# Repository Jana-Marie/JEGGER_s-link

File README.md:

# JEGGER s-link

[https://twitter.com/_Jana_Marie/status/1245725762642206728](https://twitter.com/_Jana_Marie/status/1245725762642206728)

-------

[https://github.com/ARMmbed/DAPLink](https://github.com/ARMmbed/DAPLink)

-------

https://github.com/blacksphere/blackmagic/wiki

-------

[.](https://weekly-geekly.github.io/articles/442290/index.html)
[.](https://www.segger.com/products/debug-probes/j-link/models/other-j-links/st-link-on-board/)

Go figure it out for yourself

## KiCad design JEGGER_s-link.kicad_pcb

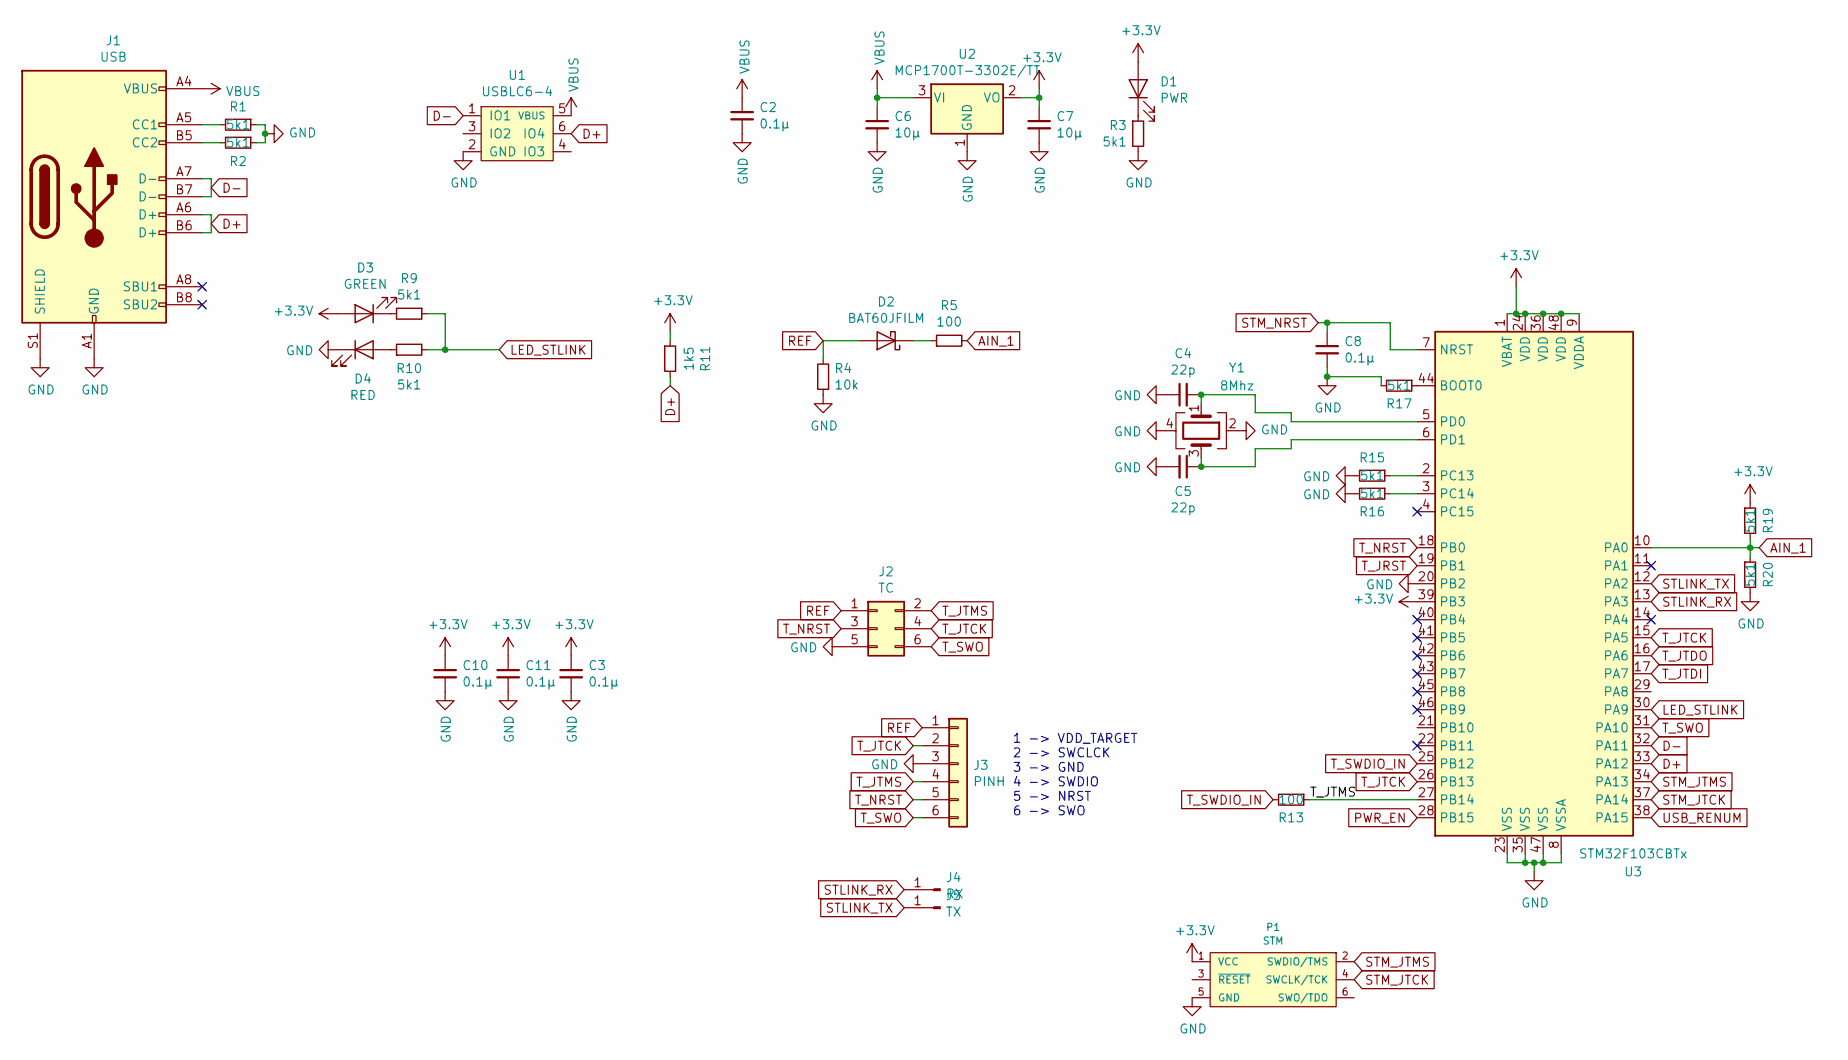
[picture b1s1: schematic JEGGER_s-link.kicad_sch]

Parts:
C2, C3, C8, C10, C11: 0.1µ; C_0402
C4, C5: 22p; C_0402
C6, C7: 10µ; C_0402
D1: PWR; LED_0603_1608Metric
D2: BAT60JFILM; D_SOD-323
D3: GREEN; LED_0603_1608Metric
D4: RED; LED_0603_1608Metric
J1: USB; USB-C 16Pin
J2: TC; IDC-Header_2x03_P2.54mm_Vertical_center
J3: PINH; PinHeader_1x06_P2.54mm_Vertical_center
J4: RX; TestPoint_Pad_1.0x1.0mm
J5: TX; TestPoint_Pad_1.0x1.0mm
P1: STM; TC2030
R1, R2, R3, R9, R10, R15, R16, R17, R19, R20: 5k1; R_0402
R4: 10k; R_0402
R5, R13: 100; R_0402
R11: 1k5; R_0402
U1: USBLC6-4; SOT-23-6
U2: MCP1700T-3302E/TT; SOT-23
U3: STM32F103CBTx; LQFP-48_7x7mm_P0.5mm
Y1: 8Mhz; Crystal_SMD_3225-4Pin_3.2x2.5mm

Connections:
+3V3: C3.1, C7.1, C10.1, C11.1, D1.2 (A), D3.2 (A), P1.1 (VCC), R11.1, R19.1, U2.2 (VO), U3.1 (VBAT), U3.9 (VDDA), U3.24 (VDD), U3.36 (VDD), U3.39 (PB3), U3.48 (VDD)
AIN_1: R5.2, R19.2, R20.1, U3.10 (PA0)
D+: J1.A6 (D+), J1.B6 (D+), R11.2, U1.6 (IO4), U3.33 (PA12)
D-: J1.A7 (D-), J1.B7 (D-), U1.1 (IO1), U3.32 (PA11)
GND: C2.2, C3.2, C4.1, C5.2, C6.2, C7.2, C8.2, C10.2, C11.2, D4.1 (K), J1.A1 (GND), J1.A12 (GND), J1.B1 (GND), J1.B12 (GND), J1.S1 (SHIELD), J2.5, J3.3, P1.5 (GND), R1.1, R2.1, R3.2, R4.1, R15.2, R16.2, R17.2, R20.2, U1.2 (GND), U2.1 (GND), U3.8 (VSSA), U3.20 (PB2), U3.23 (VSS), U3.35 (VSS), U3.47 (VSS), Y1.2, Y1.4
LED_STLINK: R9.1, R10.2, U3.30 (PA9)
unnamed: C4.2, U3.5 (PD0), Y1.1
unnamed: C5.1, U3.6 (PD1), Y1.3
unnamed: D1.1 (K), R3.1
unnamed: D2.1 (K), R5.1
unnamed: D3.1 (K), R9.2
unnamed: D4.2 (A), R10.1
unnamed: J1.A5 (CC1), R1.2
unnamed: J1.B5 (CC2), R2.2
unnamed: R15.1, U3.2 (PC13)
unnamed: R16.1, U3.3 (PC14)
unnamed: R17.1, U3.44 (BOOT0)
PWR_EN: U3.28 (PB15)
REF: D2.2 (A), J2.1, J3.1, R4.2
STLINK_RX: J4.1, U3.13 (PA3)
STLINK_TX: J5.1, U3.12 (PA2)
STM_JTCK: P1.4 (SWCLK/TCK), U3.37 (PA14)
STM_JTMS: P1.2 (SWDIO/TMS), U3.34 (PA13)
STM_NRST: C8.1, U3.7 (NRST)
T_JRST: U3.19 (PB1)
T_JTCK: J2.4, J3.2, U3.15 (PA5), U3.26 (PB13)
T_JTDI: U3.17 (PA7)
T_JTDO: U3.16 (PA6)
T_JTMS: J2.2, J3.4, R13.1, U3.27 (PB14)
T_NRST: J2.3, J3.5, U3.18 (PB0)
T_SWDIO_IN: R13.2, U3.25 (PB12)
T_SWO: J2.6, J3.6, U3.31 (PA10)
USB_RENUM: U3.38 (PA15)
VBUS: C2.1, C6.1, J1.A4 (VBUS), J1.A9 (VBUS), J1.B4 (VBUS), J1.B9 (VBUS), U1.5 (VBUS), U2.3 (VI)

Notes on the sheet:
1 -> VDD_TARGET 2 -> SWCLCK 3 -> GND 4 -> SWDIO 5 -> NRST 6 -> SWO

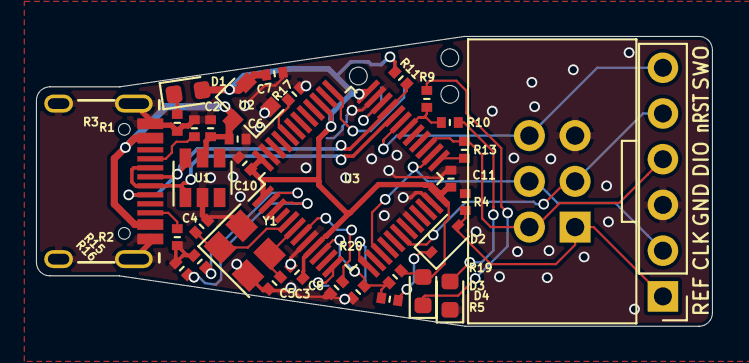
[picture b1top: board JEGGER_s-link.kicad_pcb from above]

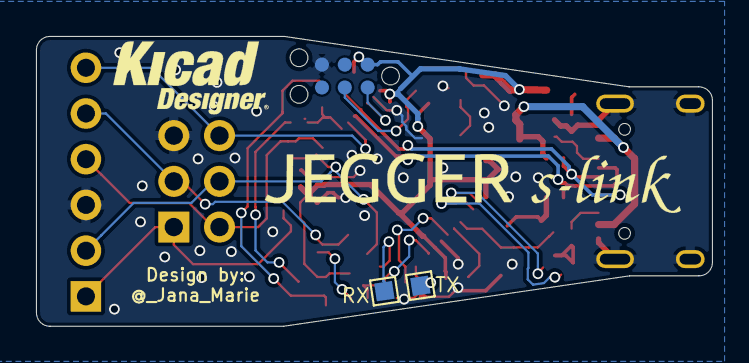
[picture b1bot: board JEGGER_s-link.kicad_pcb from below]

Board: 2 copper layers, 37.6 x 16.1 mm, 37 parts (3 on the bottom side), 29 nets.

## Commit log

2020-03-16 added gitignore
2020-03-16 finished layout, renamed, added gerber
2020-03-16 removed old files
2020-04-02 updated files
2020-04-02 push
2022-01-09 updated to KiCAD 6
